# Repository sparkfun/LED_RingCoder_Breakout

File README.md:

**NOTE:** *This product has been retired from our catalog. If you are looking for more up-to-date info, please check out some of these resources to see how other users are still hacking and improving on this product.*
* *[SparkFun Forum](https://forum.sparkfun.com/)*
* *[Comments Here on GitHub](https://github.com/sparkfun/LED_RingCoder_Breakout/issues)*
* *[IRC Channel](https://www.sparkfun.com/news/263)*

LED RingCoder Breakout - RGB
============================

[  
*LED RingCoder Breakout-RGB (BOB-11040)*](https://www.sparkfun.com/products/11040)

This breakout board gives you a pretty slick interface for rotary input. This board uses two 8-bit shift registers to control a circular
LED bargraph which can be used to indicate the virtual position of a rotary encoder. 

Repository Contents
-------------------
* **/Firmware** - Example Arduino sketch to use with this board 
* **/Hardware** - All Eagle design files (.brd, .sch)
* **/Production** - Test bed files and production panel files

Product Versions
----------------

Compatible with the following rotary encoder and LED bar graphs: 

* [COM-10982](https://www.sparkfun.com/products/10982)- RGB rotary encoder-illuminated.
* [COM-10591](https://www.sparkfun.com/products/retired/10591)- Circular LED Bargraphs - Green
* [COM-10592](https://www.sparkfun.com/products/retired/10592)- Circular LED Bargraphs - Blue
* [COM-10593](https://www.sparkfun.com/products/retired/10593)- Circular LED Bargraphs - Yellow
* [COM-10595](https://www.sparkfun.com/products/retired/10595)- Circular LED Bargraphs - Red

Version History
---------------
* [Version 1.4](https://www.sparkfun.com/products/11040)

License Information
-------------------
The hardware is released under [Creative Commons Share-alike 3.0](http://creativecommons.org/licenses/by-sa/3.0/).  
All other code is open source so please feel free to do anything you want with it; you buy me a beer if you use this and we meet someday ([Beerware license](http://en.wikipedia.org/wiki/Beerware)).

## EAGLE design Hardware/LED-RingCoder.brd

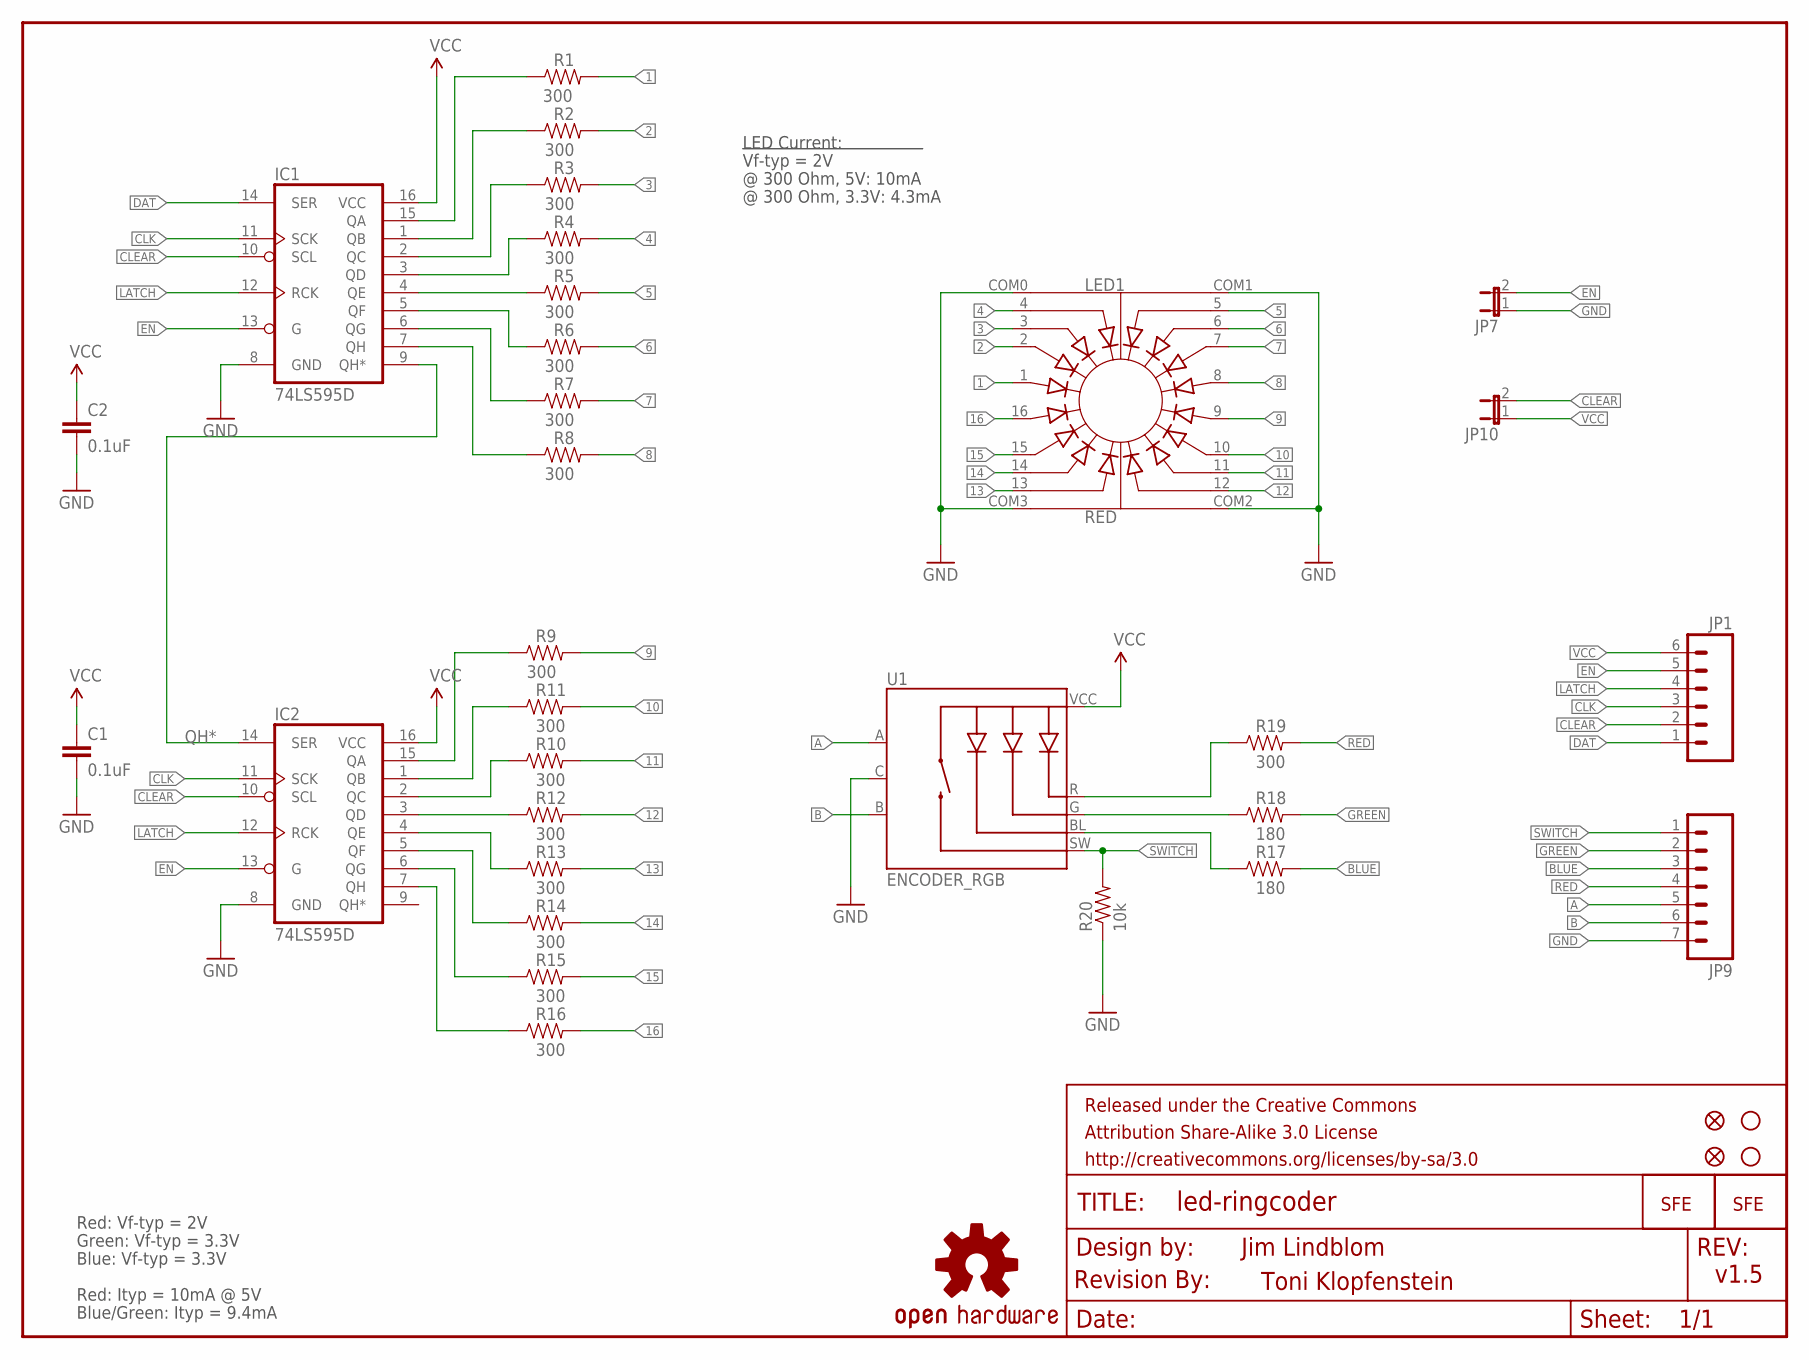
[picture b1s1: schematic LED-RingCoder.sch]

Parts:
C1, C2: 0.1uF; 0603-CAP
FRAME1: FRAME-LETTER; CREATIVE_COMMONS
IC1, IC2: 74LS595D; SO16
JP1: M06SIP; 1X06
JP2: LOGO-SFENW2; SFE-NEW-WEB
JP3, JP4: STAND-OFF
JP5, JP8: FIDUCIAL1X2.5; FIDUCIAL-1X2.5
JP6: LOGO-SFESK; SFE-LOGO-FLAME
JP7, JP10: JUMPER-2SMD-NC; SJ_2S
JP9: M07; 1X07
LED1: RED; LED_RING
R1, R2, R3, R4, R5, R6, R7, R8, R9, R10, R11, R12, R13, R14, R15, R16, R19: 300; 0603-RES
R17, R18: 180; 0603-RES
R20: 10k; 0603-RES
U1: ENCODER_RGB; ENCODER_LED_RGB
U$1: REVISION
U$2: OSHW-LOGOS; OSHW-LOGO-S

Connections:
1: LED1.1, R1.2
2: LED1.2, R2.2
3: LED1.3, R3.2
4: LED1.4, R4.2
5: LED1.5, R5.2
6: LED1.6, R6.2
7: LED1.7, R7.2
8: LED1.8, R8.2
9: LED1.9, R9.2
10: LED1.10, R11.2
11: LED1.11, R10.2
12: LED1.12, R12.2
13: LED1.13, R13.2
14: LED1.14, R14.2
15: LED1.15, R15.2
16: LED1.16, R16.2
A: JP9.5, U1.A
B: JP9.6, U1.B
BLUE: JP9.3, R17.2
CLEAR: IC1.10 (SCL), IC2.10 (SCL), JP1.2, JP10.2
CLK: IC1.11 (SCK), IC2.11 (SCK), JP1.3
DAT: IC1.14 (SER), JP1.1
EN: IC1.13 (G), IC2.13 (G), JP1.5, JP7.2
GND: C1.2, C2.2, IC1.8 (GND), IC2.8 (GND), JP7.1, JP9.7, LED1.COM0, LED1.COM1, LED1.COM2, LED1.COM3, R20.1, U1.C
GREEN: JP9.2, R18.2
LATCH: IC1.12 (RCK), IC2.12 (RCK), JP1.4
LED-B: R17.1, U1.BL
LED-G: R18.1, U1.G
LED-R: R19.1, U1.R
unnamed: IC1.15 (QA), R1.1
unnamed: IC1.1 (QB), R2.1
unnamed: IC1.2 (QC), R3.1
unnamed: IC1.3 (QD), R4.1
unnamed: IC1.4 (QE), R5.1
unnamed: IC1.5 (QF), R6.1
unnamed: IC1.6 (QG), R7.1
unnamed: IC1.7 (QH), R8.1
unnamed: IC2.15 (QA), R9.1
unnamed: IC2.1 (QB), R11.1
unnamed: IC2.2 (QC), R10.1
unnamed: IC2.3 (QD), R12.1
unnamed: IC2.4 (QE), R13.1
unnamed: IC2.5 (QF), R14.1
unnamed: IC2.6 (QG), R15.1
unnamed: IC2.7 (QH), R16.1
QH*: IC1.9 (QH*), IC2.14 (SER)
RED: JP9.4, R19.2
SWITCH: JP9.1, R20.2, U1.SW
VCC: C1.1, C2.1, IC1.16 (VCC), IC2.16 (VCC), JP1.6, JP10.1, U1.VCC

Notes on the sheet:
Jim Lindblom
Vf-typ = 2V
@ 300 Ohm, 5V: 10mA
LED Current:
Red: Vf-typ = 2V
Green: Vf-typ = 3.3V
Blue: Vf-typ = 3.3V
@ 300 Ohm, 3.3V: 4.3mA
Red: Ityp = 10mA @ 5V
Blue/Green: Ityp = 9.4mA
v1.5
Toni Klopfenstein

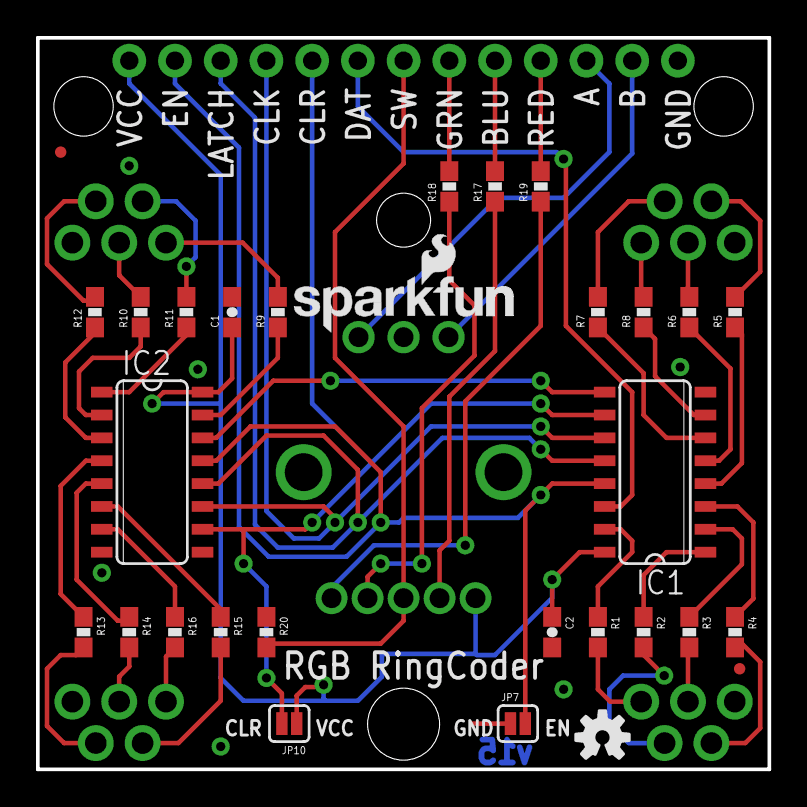
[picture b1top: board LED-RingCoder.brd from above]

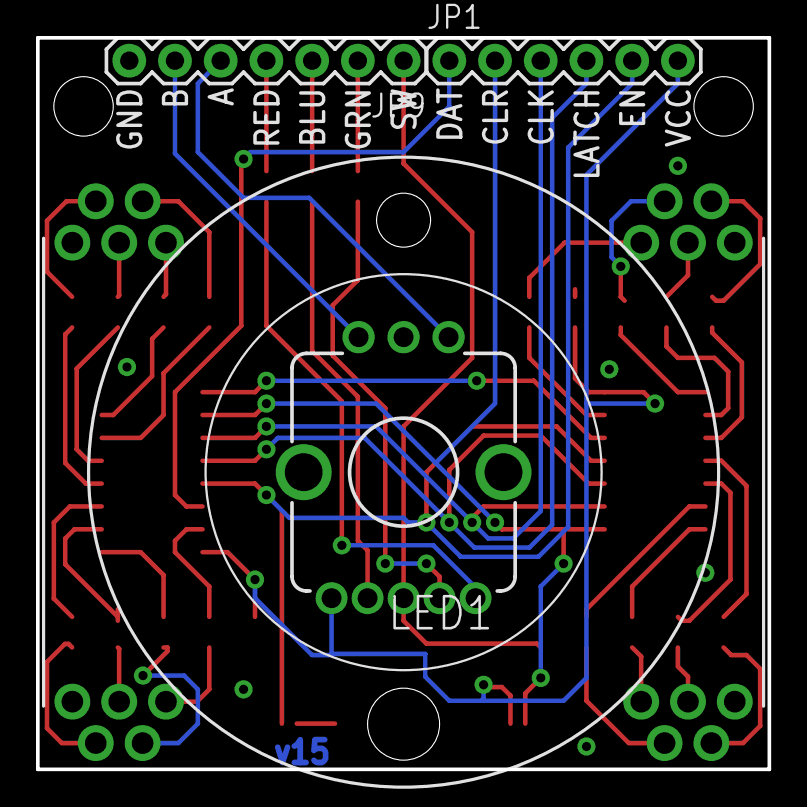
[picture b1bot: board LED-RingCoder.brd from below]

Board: 2 copper layers, 40.6 x 40.6 mm, 39 parts (6 on the bottom side), 49 nets.

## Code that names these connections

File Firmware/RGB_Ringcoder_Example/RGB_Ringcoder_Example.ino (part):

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int redPin = 5;  // Encoder's red LED - D5 is PWM enabled
int bluPin = 6;  // Encoder's blue LED- D6 is PWM enabled
int grnPin = 9;  // Encoder's green LED - D9 is PWM enabled
int swhPin = 7;  // Encoder's switch pin

// Pin definitions - Shift registers:
int enPin = 13;  // Shift registers' Output Enable pin
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  attachInterrupt(0, readEncoder, CHANGE);
  attachInterrupt(1, readEncoder, CHANGE);
  
  // setup switch pins, set as an input, no pulled up
  pinMode(swhPin, INPUT);
  digitalWrite(swhPin, LOW);  // Disable internal pull-up
  
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  pinMode(enPin, OUTPUT);  // Enable, active low, this'll always be LOW
  digitalWrite(enPin, LOW);  // Turn all outputs on
  pinMode(latchPin, OUTPUT);  // this must be set before calling shiftOut16()
  digitalWrite(latchPin, LOW);  // start latch low
  pinMode(clkPin, OUTPUT);  // we'll control this in shiftOut16()
  digitalWrite(clkPin, LOW);  // start sck low
  pinMode(clrPin, OUTPUT);  // master clear, this'll always be HIGH
  digitalWrite(clrPin, HIGH);  // disable master clear
  pinMode(datPin, OUTPUT);  // we'll control this in shiftOut16()
  digitalWrite(datPin, LOW);  // start ser low
  
  // To begin, we'll turn all LEDs on the circular bar-graph OFF
  digitalWrite(latchPin, LOW);  // first send latch low
  shiftOut16(0x0000);
  digitalWrite(latchPin, HIGH);  // send latch high to indicate data is done sending
    
  // Now we can enable interrupts and start the code.
  interrupts(); 
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  // Now we just need to write to the shift registers. We have to
  // control latch manually, but shiftOut16 will take care of
  // everything else.
  digitalWrite(latchPin, LOW);  // first send latch low
  shiftOut16(ledOutput);  // send the ledOutput value to shiftOut16
  digitalWrite(latchPin, HIGH);  // send latch high to indicate data is done sending 
}

// void ledRingFollower(byte rotationSpeed) - This is one of two
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  // Now we just need to write to the shift registers. We have to
  // control latch manually, but shiftOut16 will take care of
  // everything else.
  digitalWrite(latchPin, LOW);  // first send latch low
  shiftOut16(ledOutput);  // send the ledOutput value to shiftOut16
  digitalWrite(latchPin, HIGH);  // send latch high to indicate data is done sending 
}

// This function'll call shiftOut (a pre-defined Arduino function)
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
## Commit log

2013-08-12 Initial file commit
2014-01-23 Adding v15 files
2014-01-28 Adding EN/GND and CLR/VCC jumpers
2014-01-30 Moving VCC/CLR jumper

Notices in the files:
Firmware/RGB_Ringcoder_Example/RGB_Ringcoder_Example.ino:
license: Beerware - Consider this code open domain, please use it
parts and their libraries:
SparkFun-Aesthetics: Licensing: CC v3.0 Share-Alike You are welcome to use this library for commercial purposes.
SparkFun-Aesthetics: Released under the Creative Commons Attribution Share-Alike 3.0 License
SparkFun-Aesthetics: Released under the Creative Commons
